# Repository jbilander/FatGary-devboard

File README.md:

# FatGary-devboard
A development board for the Fat Gary chip.

***

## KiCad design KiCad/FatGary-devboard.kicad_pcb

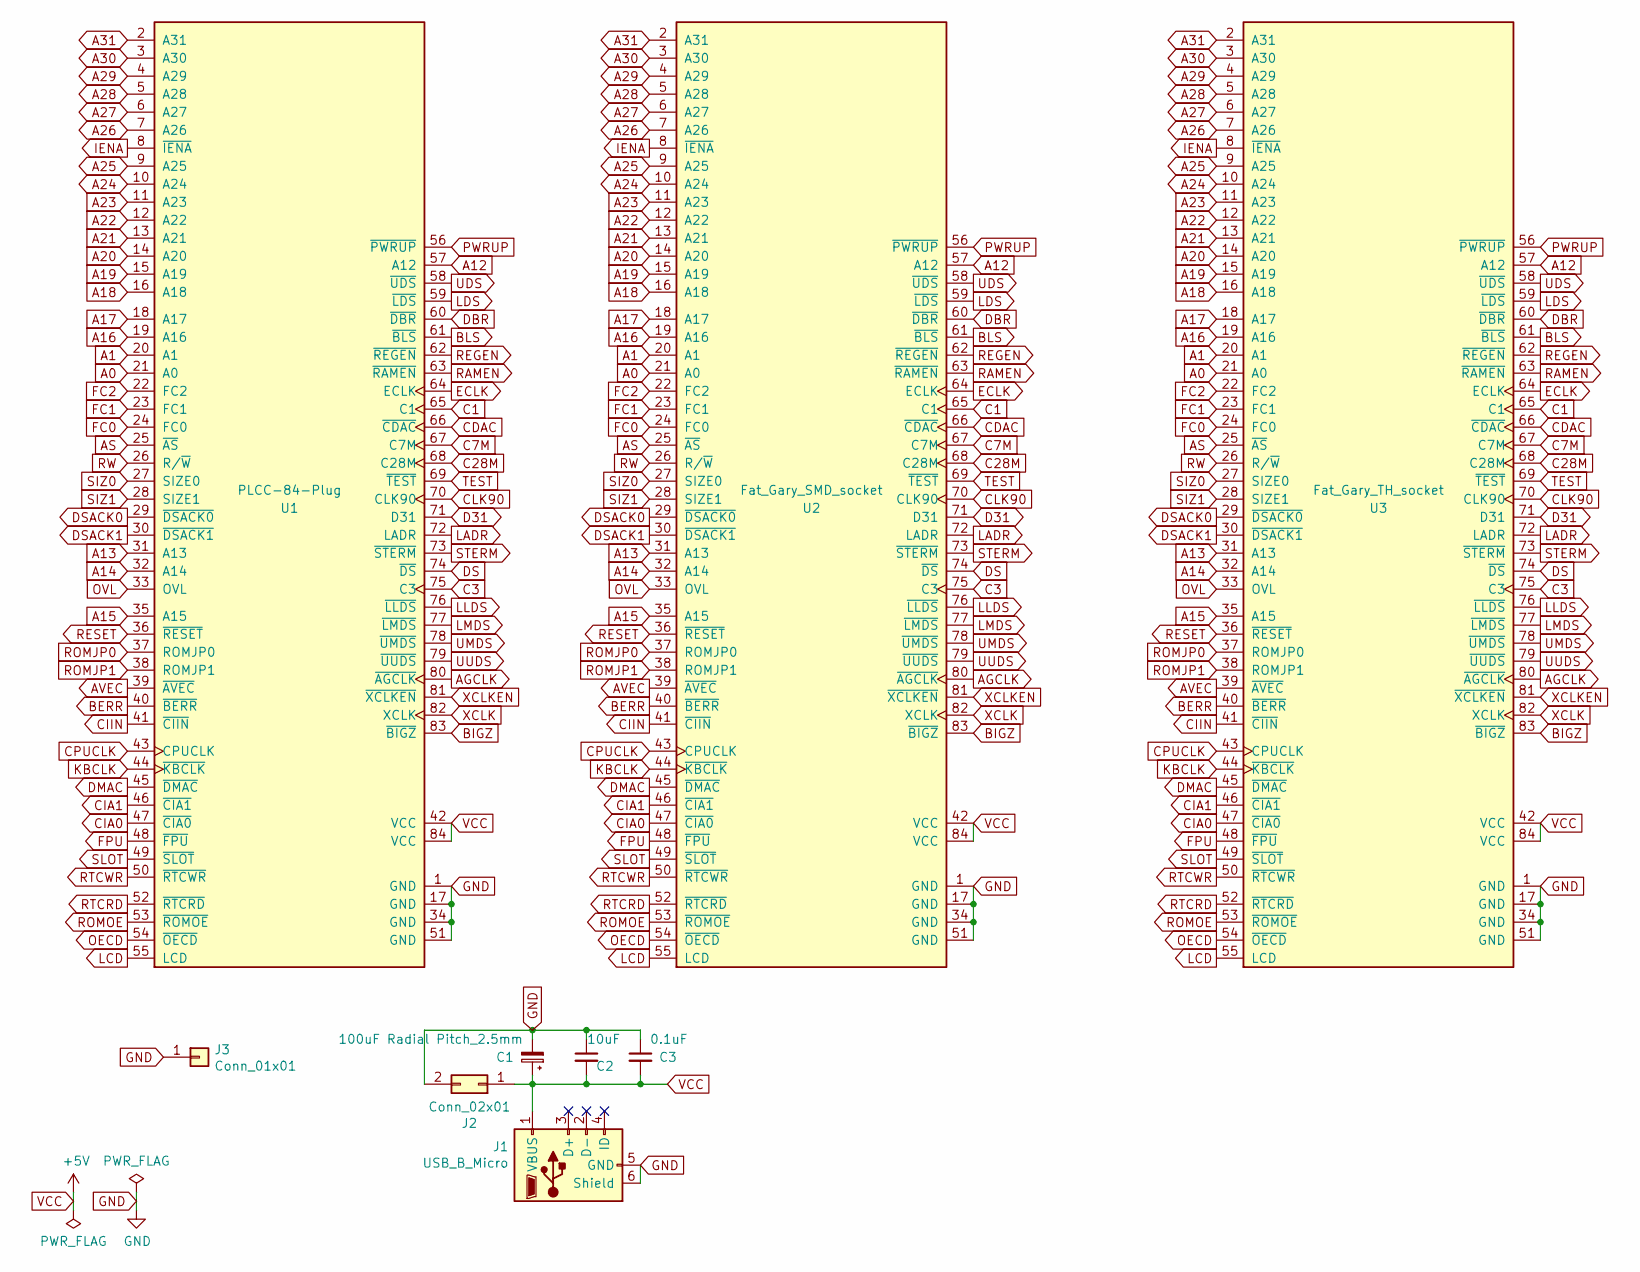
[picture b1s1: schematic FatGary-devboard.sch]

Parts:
C1: 100uF Radial Pitch_2.5mm; CP_Radial_D5.0mm_P2.50mm
C2: 10uF; C_1206_3216Metric_Pad1.33x1.80mm_HandSolder
C3: 0.1uF; C_0805_2012Metric_Pad1.18x1.45mm_HandSolder
J1: USB_B_Micro; USB_Micro-B_Unknown_5s_SMT
J2: Conn_02x01; PinHeader_2x01_P2.54mm_Vertical
J3: Conn_01x01; MountingHole_3.2mm_M3_Pad_Via
U1: PLCC-84-Plug; PLCC-84_Plug_P1.27mm_mirrored_extended_pads
U2: Fat_Gary_SMD_socket; PLCC-84_SMD-Socket_TH_modded
U3: Fat_Gary_TH_socket; PLCC-84_THT-Socket

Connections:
A0: U1.21 (A0), U2.21 (A0), U3.21 (A0)
A1: U1.20 (A1), U2.20 (A1), U3.20 (A1)
A12: U1.57 (A12), U2.57 (A12), U3.57 (A12)
A13: U1.31 (A13), U2.31 (A13), U3.31 (A13)
A14: U1.32 (A14), U2.32 (A14), U3.32 (A14)
A15: U1.35 (A15), U2.35 (A15), U3.35 (A15)
A16: U1.19 (A16), U2.19 (A16), U3.19 (A16)
A17: U1.18 (A17), U2.18 (A17), U3.18 (A17)
A18: U1.16 (A18), U2.16 (A18), U3.16 (A18)
A19: U1.15 (A19), U2.15 (A19), U3.15 (A19)
A20: U1.14 (A20), U2.14 (A20), U3.14 (A20)
A21: U1.13 (A21), U2.13 (A21), U3.13 (A21)
A22: U1.12 (A22), U2.12 (A22), U3.12 (A22)
A23: U1.11 (A23), U2.11 (A23), U3.11 (A23)
A24: U1.10 (A24), U2.10 (A24), U3.10 (A24)
A25: U1.9 (A25), U2.9 (A25), U3.9 (A25)
A26: U1.7 (A26), U2.7 (A26), U3.7 (A26)
A27: U1.6 (A27), U2.6 (A27), U3.6 (A27)
A28: U1.5 (A28), U2.5 (A28), U3.5 (A28)
A29: U1.4 (A29), U2.4 (A29), U3.4 (A29)
A30: U1.3 (A30), U2.3 (A30), U3.3 (A30)
A31: U1.2 (A31), U2.2 (A31), U3.2 (A31)
AGCLK: U1.80 (~AGCLK), U2.80 (~AGCLK), U3.80 (~AGCLK)
AS: U1.25 (~AS), U2.25 (~AS), U3.25 (~AS)
AVEC: U1.39 (~AVEC), U2.39 (~AVEC), U3.39 (~AVEC)
BERR: U1.40 (~BERR), U2.40 (~BERR), U3.40 (~BERR)
BIGZ: U1.83 (~BIGZ), U2.83 (~BIGZ), U3.83 (~BIGZ)
BLS: U1.61 (~BLS), U2.61 (~BLS), U3.61 (~BLS)
C1: U1.65 (C1), U2.65 (C1), U3.65 (C1)
C3: U1.75 (C3), U2.75 (C3), U3.75 (C3)
C7M: U1.67 (C7M), U2.67 (C7M), U3.67 (C7M)
C28M: U1.68 (C28M), U2.68 (C28M), U3.68 (C28M)
CDAC: U1.66 (~CDAC), U2.66 (~CDAC), U3.66 (~CDAC)
CIA0: U1.47 (~CIA0), U2.47 (~CIA0), U3.47 (~CIA0)
CIA1: U1.46 (~CIA1), U2.46 (~CIA1), U3.46 (~CIA1)
CIIN: U1.41 (~CIIN), U2.41 (~CIIN), U3.41 (~CIIN)
CLK90: U1.70 (CLK90), U2.70 (CLK90), U3.70 (CLK90)
CPUCLK: U1.43 (CPUCLK), U2.43 (CPUCLK), U3.43 (CPUCLK)
D31: U1.71 (D31), U2.71 (D31), U3.71 (D31)
DBR: U1.60 (~DBR), U2.60 (~DBR), U3.60 (~DBR)
DMAC: U1.45 (~DMAC), U2.45 (~DMAC), U3.45 (~DMAC)
DS: U1.74 (~DS), U2.74 (~DS), U3.74 (~DS)
DSACK0: U1.29 (~DSACK0), U2.29 (~DSACK0), U3.29 (~DSACK0)
DSACK1: U1.30 (~DSACK1), U2.30 (~DSACK1), U3.30 (~DSACK1)
ECLK: U1.64 (ECLK), U2.64 (ECLK), U3.64 (ECLK)
FC0: U1.24 (FC0), U2.24 (FC0), U3.24 (FC0)
FC1: U1.23 (FC1), U2.23 (FC1), U3.23 (FC1)
FC2: U1.22 (FC2), U2.22 (FC2), U3.22 (FC2)
FPU: U1.48 (~FPU), U2.48 (~FPU), U3.48 (~FPU)
GND: C1.2, C2.1, C3.1, J1.5 (GND), J1.6 (Shield), J2.2, J3.1, U1.1 (GND), U1.17 (GND), U1.34 (GND), U1.51 (GND), U2.1 (GND), U2.17 (GND), U2.34 (GND), U2.51 (GND), U3.1 (GND), U3.17 (GND), U3.34 (GND), U3.51 (GND)
IENA: U1.8 (~IENA), U2.8 (~IENA), U3.8 (~IENA)
KBCLK: U1.44 (~KBCLK), U2.44 (~KBCLK), U3.44 (~KBCLK)
LADR: U1.72 (LADR), U2.72 (LADR), U3.72 (LADR)
LCD: U1.55 (LCD), U2.55 (LCD), U3.55 (LCD)
LDS: U1.59 (~LDS), U2.59 (~LDS), U3.59 (~LDS)
LLDS: U1.76 (~LLDS), U2.76 (~LLDS), U3.76 (~LLDS)
LMDS: U1.77 (~LMDS), U2.77 (~LMDS), U3.77 (~LMDS)
OECD: U1.54 (~OECD), U2.54 (~OECD), U3.54 (~OECD)
OVL: U1.33 (OVL), U2.33 (OVL), U3.33 (OVL)
PWRUP: U1.56 (~PWRUP), U2.56 (~PWRUP), U3.56 (~PWRUP)
RAMEN: U1.63 (~RAMEN), U2.63 (~RAMEN), U3.63 (~RAMEN)
REGEN: U1.62 (~REGEN), U2.62 (~REGEN), U3.62 (~REGEN)
RESET: U1.36 (~RESET), U2.36 (~RESET), U3.36 (~RESET)
ROMJP0: U1.37 (ROMJP0), U2.37 (ROMJP0), U3.37 (ROMJP0)
ROMJP1: U1.38 (ROMJP1), U2.38 (ROMJP1), U3.38 (ROMJP1)
ROMOE: U1.53 (~ROMOE), U2.53 (~ROMOE), U3.53 (~ROMOE)
RTCRD: U1.52 (~RTCRD), U2.52 (~RTCRD), U3.52 (~RTCRD)
RTCWR: U1.50 (~RTCWR), U2.50 (~RTCWR), U3.50 (~RTCWR)
RW: U1.26 (R/~W), U2.26 (R/~W), U3.26 (R/~W)
SIZ0: U1.27 (SIZE0), U2.27 (SIZE0), U3.27 (SIZE0)
SIZ1: U1.28 (SIZE1), U2.28 (SIZE1), U3.28 (SIZE1)
SLOT: U1.49 (~SLOT), U2.49 (~SLOT), U3.49 (~SLOT)
STERM: U1.73 (~STERM), U2.73 (~STERM), U3.73 (~STERM)
TEST: U1.69 (~TEST), U2.69 (~TEST), U3.69 (~TEST)
UDS: U1.58 (~UDS), U2.58 (~UDS), U3.58 (~UDS)
UMDS: U1.78 (~UMDS), U2.78 (~UMDS), U3.78 (~UMDS)
UUDS: U1.79 (~UUDS), U2.79 (~UUDS), U3.79 (~UUDS)
VCC: C1.1, C2.2, C3.2, J1.1 (VBUS), J2.1, U1.42 (VCC), U1.84 (VCC), U2.42 (VCC), U2.84 (VCC), U3.42 (VCC), U3.84 (VCC)
XCLK: U1.82 (XCLK), U2.82 (XCLK), U3.82 (XCLK)
XCLKEN: U1.81 (~XCLKEN), U2.81 (~XCLKEN), U3.81 (~XCLKEN)

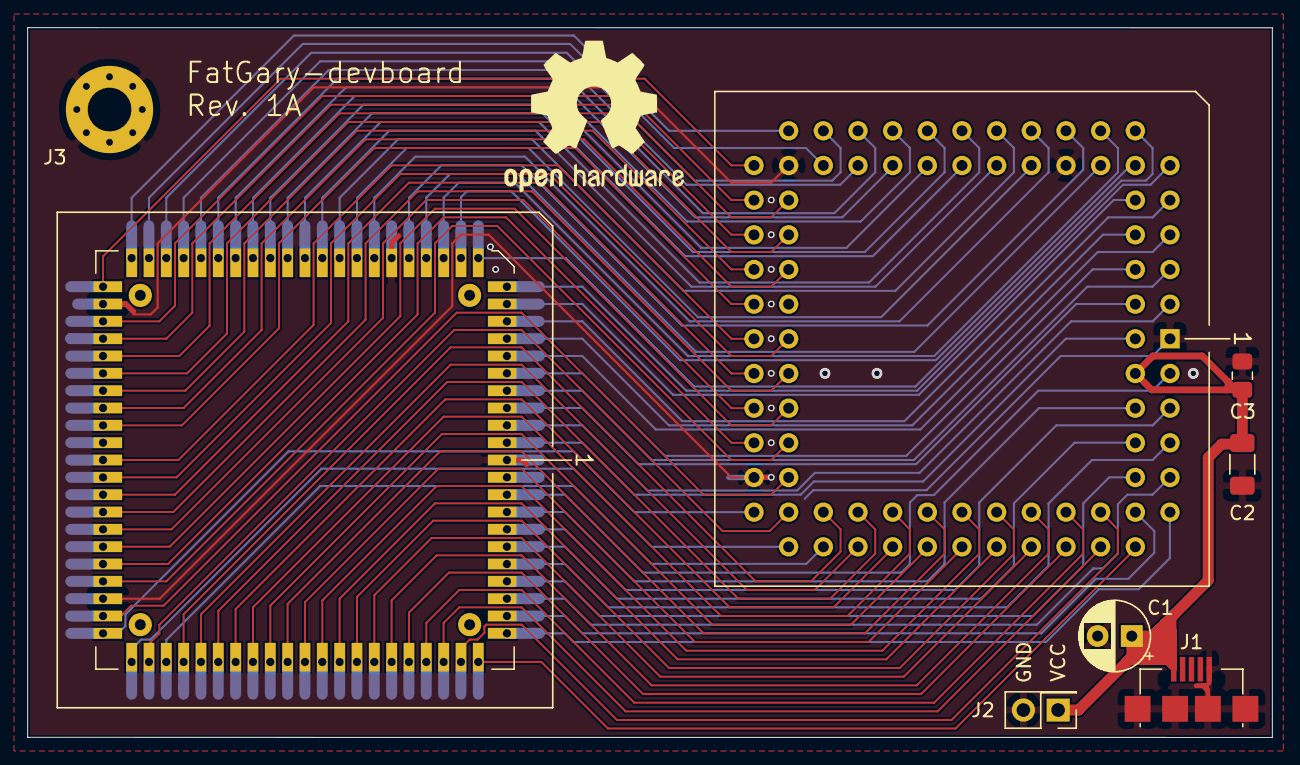
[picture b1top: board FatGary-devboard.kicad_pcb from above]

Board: 4 copper layers, 91.2 x 52.0 mm, 9 parts (1 on the bottom side), 80 nets.

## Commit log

2025-02-10 Update .gitignore file
2025-02-10 Add license file
2025-02-12 Add footprints
2025-02-12 Add KiCad files
2025-05-08 Add footprint with longer pads for the PLCC-84 smd plug
2025-05-08 Change to footprint with longer pads for the PLCC-84 smd plug
2025-06-23 Add image
